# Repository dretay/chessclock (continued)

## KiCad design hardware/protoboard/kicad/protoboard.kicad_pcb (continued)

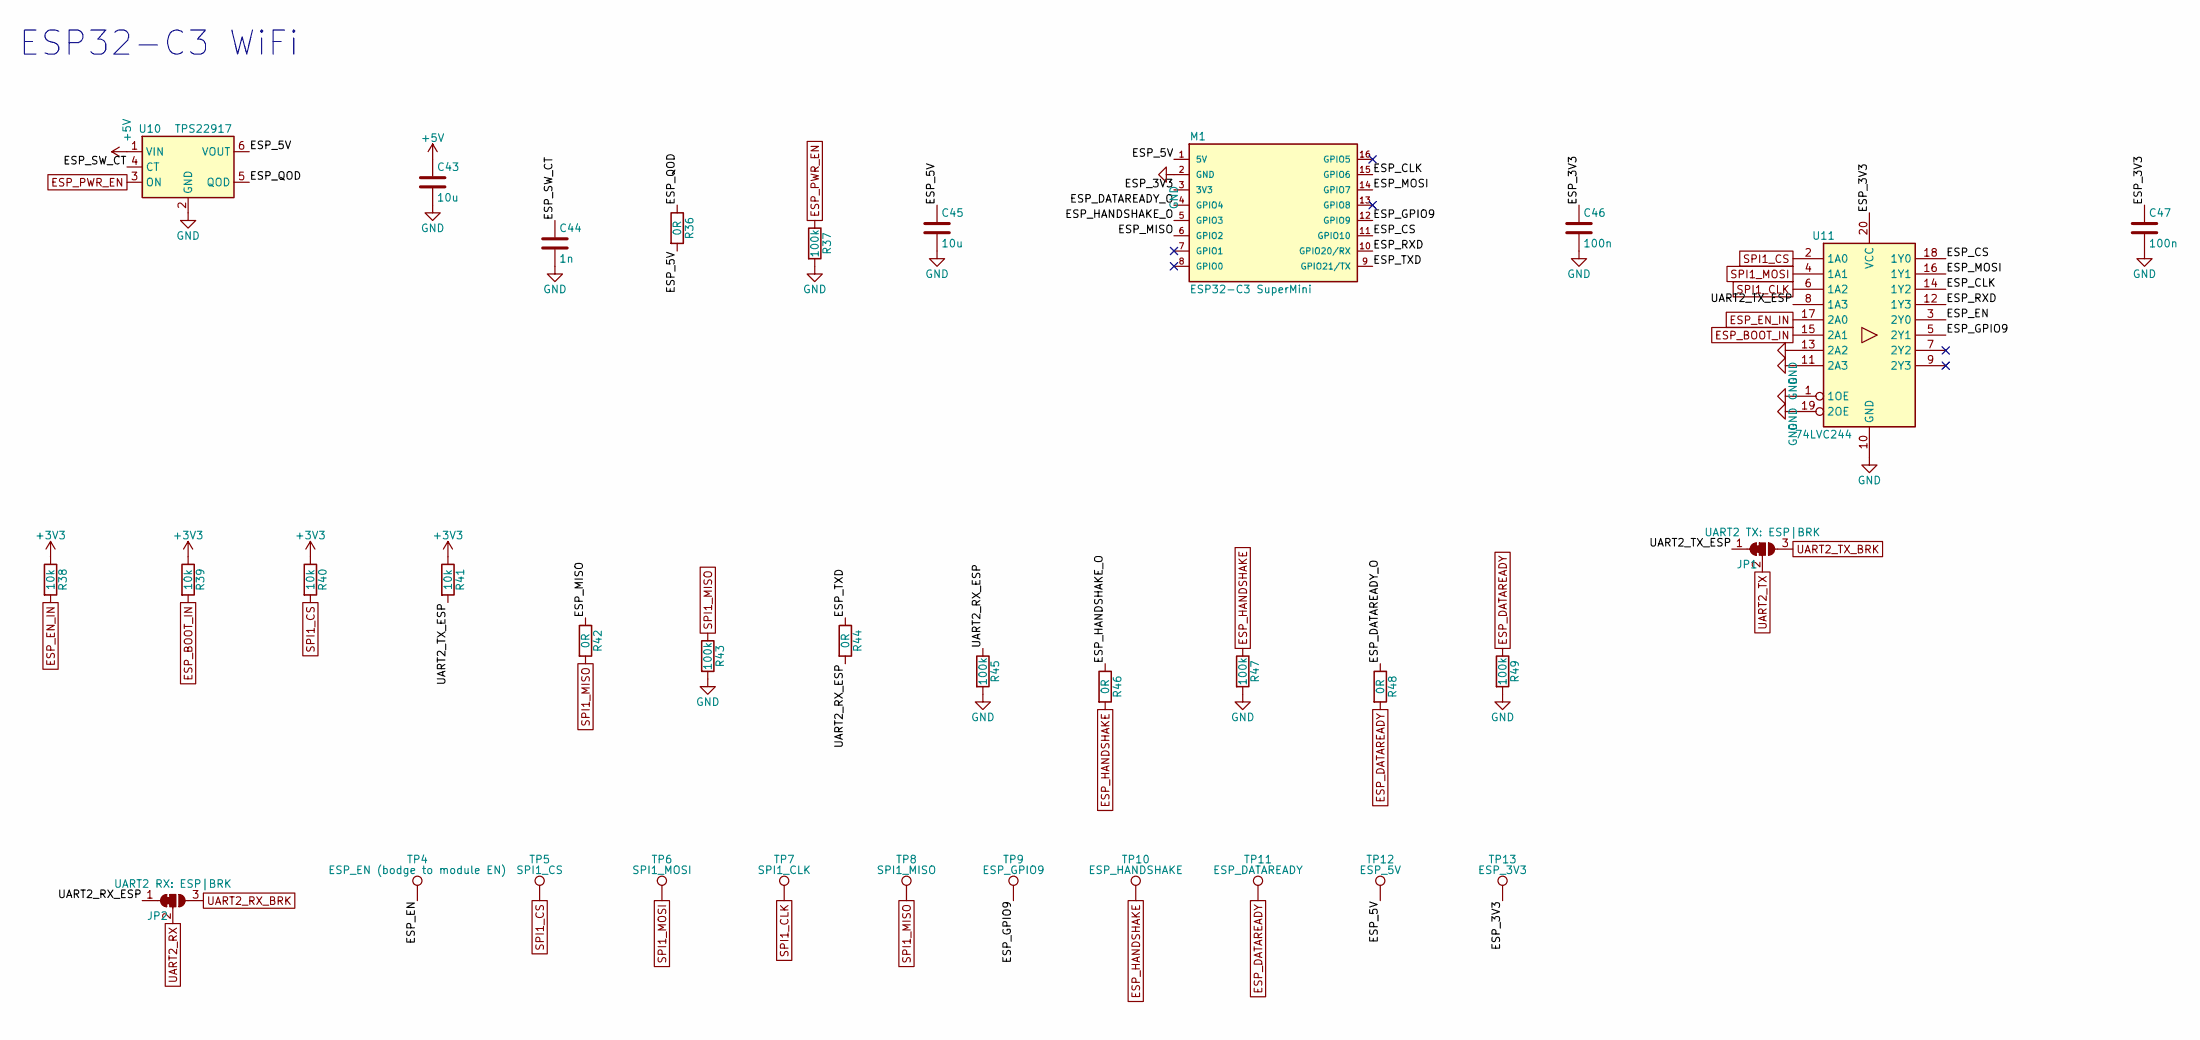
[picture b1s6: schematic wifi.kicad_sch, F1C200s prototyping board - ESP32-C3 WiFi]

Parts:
C43, C45: 10u; C_1206_3216Metric_Pad1.33x1.80mm_HandSolder
C44: 1n; C_0805_2012Metric_Pad1.18x1.45mm_HandSolder
C46, C47: 100n; C_0805_2012Metric_Pad1.18x1.45mm_HandSolder
JP1: UART2 TX: ESP|BRK; SolderJumper-3_P1.3mm_Bridged12_RoundedPad1.0x1.5mm_NumberL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
JP2: UART2 RX: ESP|BRK; SolderJumper-3_P1.3mm_Bridged12_RoundedPad1.0x1.5mm_NumberL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
M1: ESP32-C3 SuperMini; ESP32-C3_SuperMini
R36, R42, R44, R46, R48: 0R; R_0805_2012Metric_Pad1.20x1.40mm_HandSolder
R37, R43, R45, R47, R49: 100k; R_0805_2012Metric_Pad1.20x1.40mm_HandSolder
R38, R39, R40, R41: 10k; R_0805_2012Metric_Pad1.20x1.40mm_HandSolder
TP4: ESP_EN (bodge to module EN); TestPoint_Pad_D1.5mm
TP5: SPI1_CS; TestPoint_Pad_D1.5mm
TP6: SPI1_MOSI; TestPoint_Pad_D1.5mm
TP7: SPI1_CLK; TestPoint_Pad_D1.5mm
TP8: SPI1_MISO; TestPoint_Pad_D1.5mm
TP9: ESP_GPIO9; TestPoint_Pad_D1.5mm
TP10: ESP_HANDSHAKE; TestPoint_Pad_D1.5mm
TP11: ESP_DATAREADY; TestPoint_Pad_D1.5mm
TP12: ESP_5V; TestPoint_Pad_D1.5mm
TP13: ESP_3V3; TestPoint_Pad_D1.5mm
U10: TPS22917; SOT-23-6
U11: 74LVC244; SOIC-20W_7.5x12.8mm_P1.27mm

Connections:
+3V3: R38.1, R39.1, R40.1, R41.1; also elsewhere on the board
+5V: C43.1, U10.1 (VIN); also elsewhere on the board
/ESP32-C3 WiFi/ESP_3V3: C46.1, C47.1, M1.3 (3V3), TP13.1, U11.20 (VCC)
/ESP32-C3 WiFi/ESP_5V: C45.1, M1.1 (5V), R36.2, TP12.1, U10.6 (VOUT)
/ESP32-C3 WiFi/ESP_CLK: M1.15 (GPIO6), U11.14 (1Y2)
/ESP32-C3 WiFi/ESP_CS: M1.11 (GPIO10), U11.18 (1Y0)
/ESP32-C3 WiFi/ESP_DATAREADY_O: M1.4 (GPIO4), R48.1
/ESP32-C3 WiFi/ESP_EN: TP4.1, U11.3 (2Y0)
/ESP32-C3 WiFi/ESP_GPIO9: M1.12 (GPIO9), TP9.1, U11.5 (2Y1)
/ESP32-C3 WiFi/ESP_HANDSHAKE_O: M1.5 (GPIO3), R46.1
/ESP32-C3 WiFi/ESP_MISO: M1.6 (GPIO2), R42.1
/ESP32-C3 WiFi/ESP_MOSI: M1.14 (GPIO7), U11.16 (1Y1)
/ESP32-C3 WiFi/ESP_QOD: R36.1, U10.5 (QOD)
/ESP32-C3 WiFi/ESP_RXD: M1.10 (GPIO20/RX), U11.12 (1Y3)
/ESP32-C3 WiFi/ESP_SW_CT: C44.1, U10.4 (CT)
/ESP32-C3 WiFi/ESP_TXD: M1.9 (GPIO21/TX), R44.1
/ESP32-C3 WiFi/UART2_RX_ESP: JP2.1 (A), R44.2, R45.1
/ESP32-C3 WiFi/UART2_TX_ESP: JP1.1 (A), R41.2, U11.8 (1A3)
ESP_BOOT_IN: R39.2, U11.15 (2A1); also elsewhere on the board
ESP_DATAREADY: R48.2, R49.1, TP11.1; also elsewhere on the board
ESP_EN_IN: R38.2, U11.17 (2A0); also elsewhere on the board
ESP_HANDSHAKE: R46.2, R47.1, TP10.1; also elsewhere on the board
ESP_PWR_EN: R37.1, U10.3 (ON); also elsewhere on the board
GND: C43.2, C44.2, C45.2, C46.2, C47.2, M1.2 (GND), R37.2, R43.2, R45.2, R47.2, R49.2, U10.2 (GND), U11.1 (1OE), U11.10 (GND), U11.11 (2A3), U11.13 (2A2), U11.19 (2OE); also elsewhere on the board
SPI1_CLK: TP7.1, U11.6 (1A2); also elsewhere on the board
SPI1_CS: R40.2, TP5.1, U11.2 (1A0); also elsewhere on the board
SPI1_MISO: R42.2, R43.1, TP8.1; also elsewhere on the board
SPI1_MOSI: TP6.1, U11.4 (1A1); also elsewhere on the board
UART2_RX: JP2.2 (C); also elsewhere on the board
UART2_RX_BRK: JP2.3 (B); also elsewhere on the board
UART2_TX: JP1.2 (C); also elsewhere on the board
UART2_TX_BRK: JP1.3 (B); also elsewhere on the board

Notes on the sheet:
ESP32-C3 WiFi

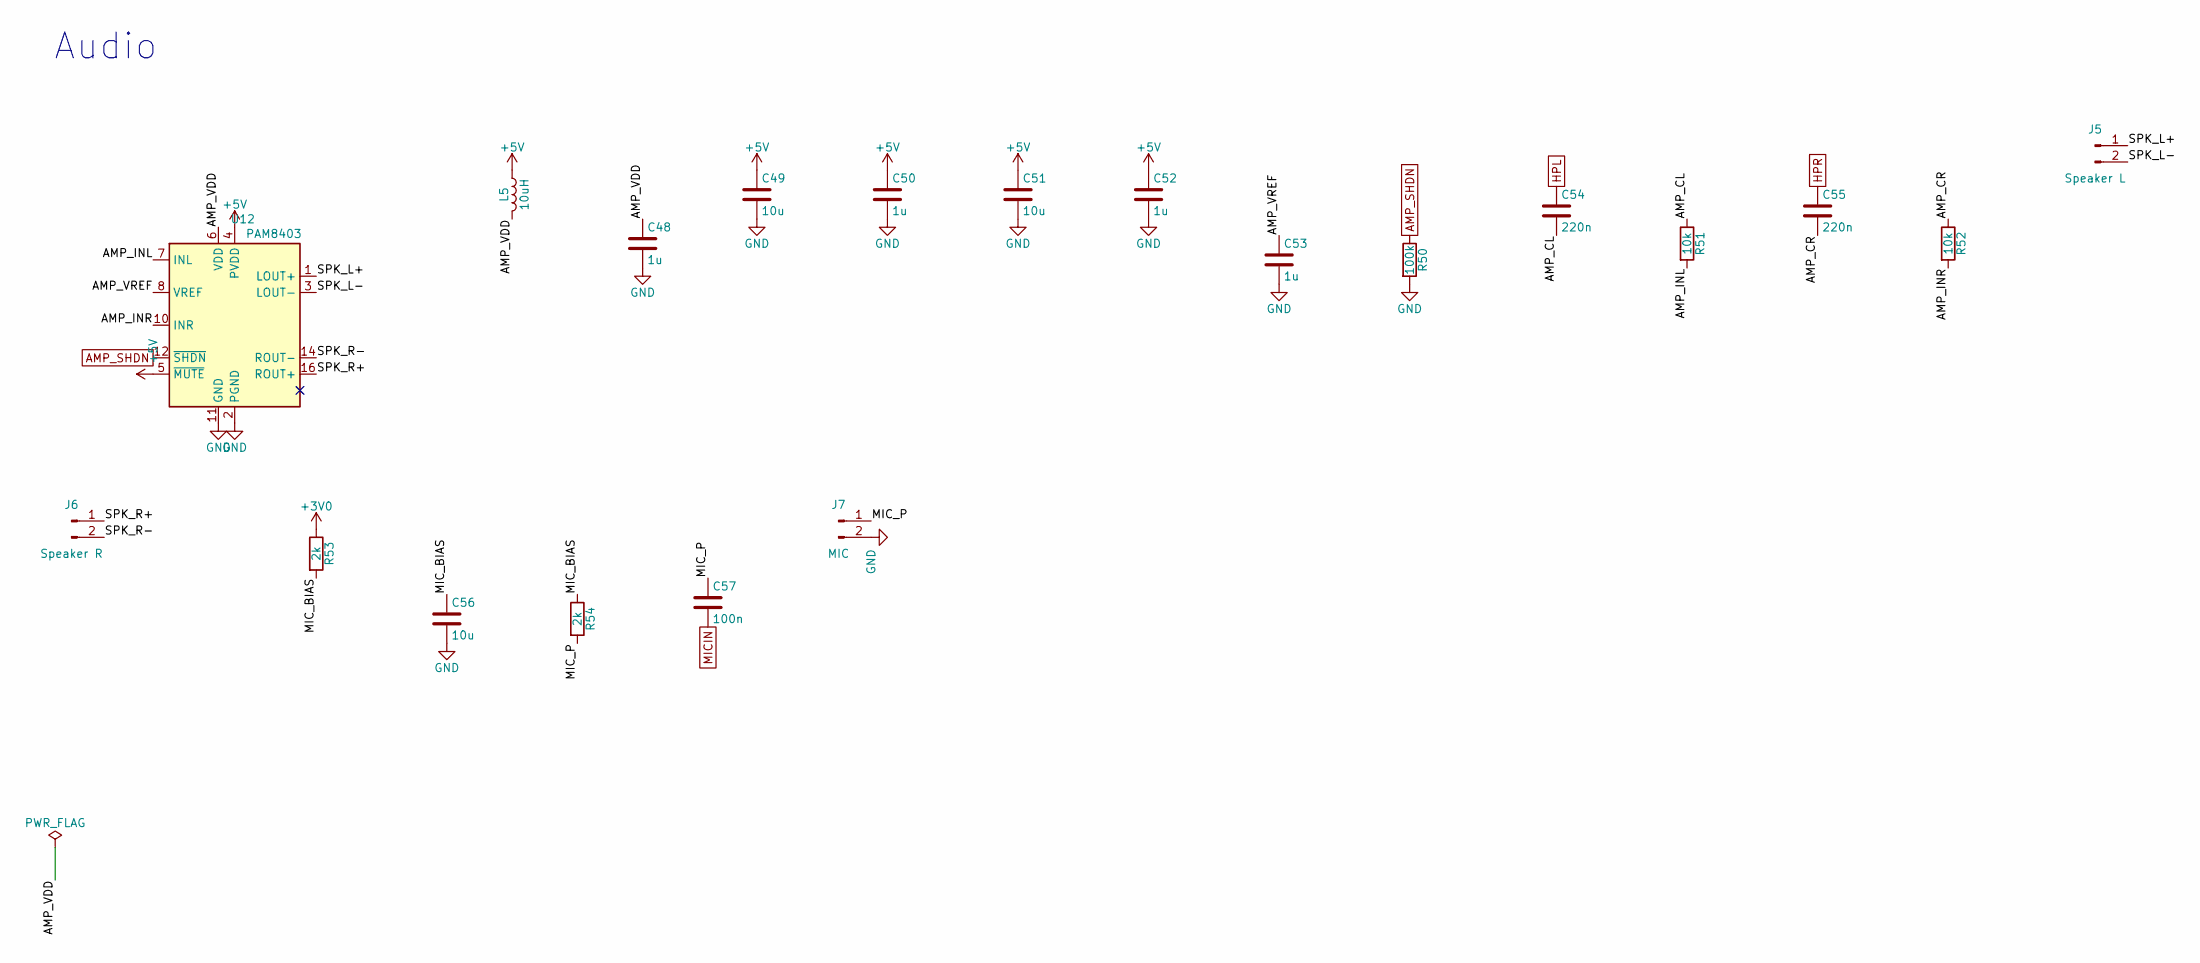
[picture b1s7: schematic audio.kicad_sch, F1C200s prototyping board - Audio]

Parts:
C48, C50, C52, C53: 1u; C_0805_2012Metric_Pad1.18x1.45mm_HandSolder
C49, C51: 10u; C_1206_3216Metric_Pad1.33x1.80mm_HandSolder
C54, C55: 220n; C_0805_2012Metric_Pad1.18x1.45mm_HandSolder
C56: 10u; C_0805_2012Metric_Pad1.18x1.45mm_HandSolder
C57: 100n; C_0805_2012Metric_Pad1.18x1.45mm_HandSolder
J5: Speaker L; JST_PH_B2B-PH-K_1x02_P2.00mm_Vertical
J6: Speaker R; JST_PH_B2B-PH-K_1x02_P2.00mm_Vertical
J7: MIC; PinHeader_1x02_P2.54mm_Vertical
L5: 10uH; L_0805_2012Metric_Pad1.05x1.20mm_HandSolder
R50: 100k; R_0805_2012Metric_Pad1.20x1.40mm_HandSolder
R51, R52: 10k; R_0805_2012Metric_Pad1.20x1.40mm_HandSolder
R53, R54: 2k; R_0805_2012Metric_Pad1.20x1.40mm_HandSolder
U12: PAM8403; SOIC-16_3.9x9.9mm_P1.27mm

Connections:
+3V0: R53.1; also elsewhere on the board
+5V: C49.1, C50.1, C51.1, C52.1, L5.1, U12.4 (PVDD), U12.5 (~MUTE), U12.13 (PVDD); also elsewhere on the board
/Audio/AMP_CL: C54.2, R51.1
/Audio/AMP_CR: C55.2, R52.1
/Audio/AMP_INL: R51.2, U12.7 (INL)
/Audio/AMP_INR: R52.2, U12.10 (INR)
/Audio/AMP_VDD: C48.1, L5.2, U12.6 (VDD)
/Audio/AMP_VREF: C53.1, U12.8 (VREF)
/Audio/MIC_BIAS: C56.1, R53.2, R54.1
/Audio/MIC_P: C57.1, J7.1, R54.2
/Audio/SPK_L+: J5.1, U12.1 (LOUT+)
/Audio/SPK_L-: J5.2, U12.3 (LOUT-)
/Audio/SPK_R+: J6.1, U12.16 (ROUT+)
/Audio/SPK_R-: J6.2, U12.14 (ROUT-)
AMP_SHDN: R50.1, U12.12 (~SHDN); also elsewhere on the board
GND: C48.2, C49.2, C50.2, C51.2, C52.2, C53.2, C56.2, J7.2, R50.2, U12.2 (PGND), U12.11 (GND), U12.15 (PGND); also elsewhere on the board
HPL: C54.1; also elsewhere on the board
HPR: C55.1; also elsewhere on the board
MICIN: C57.2; also elsewhere on the board

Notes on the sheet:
Audio

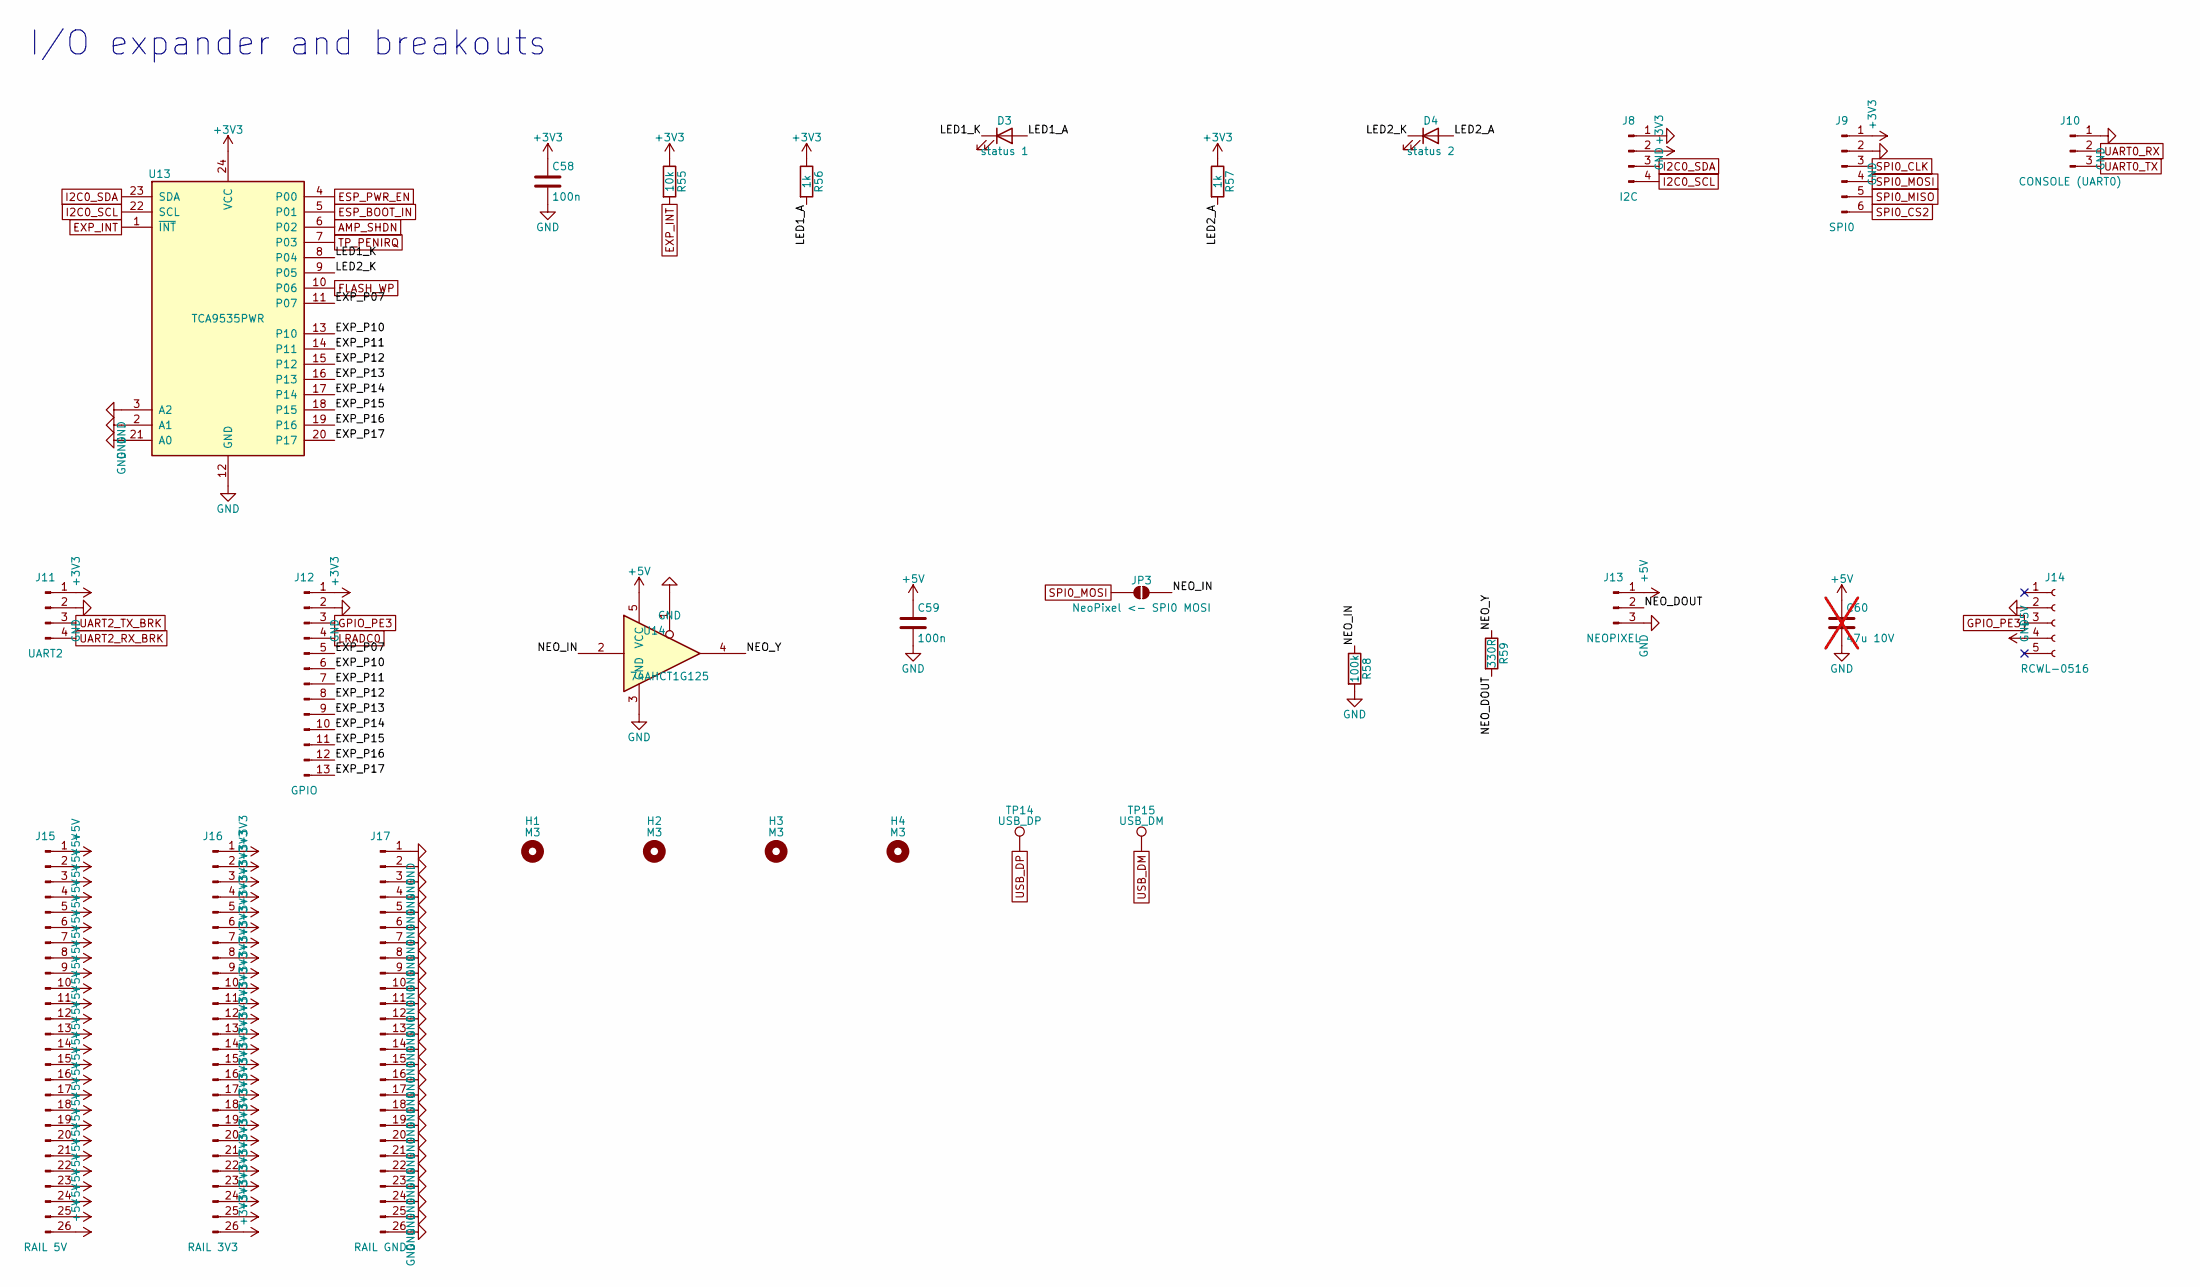
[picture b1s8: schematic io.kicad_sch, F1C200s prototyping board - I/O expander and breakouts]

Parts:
C58, C59: 100n; C_0805_2012Metric_Pad1.18x1.45mm_HandSolder
C60: 47u 10V; C_1210_3225Metric_Pad1.33x2.70mm_HandSolder; not fitted
D3: status 1; LED_0805_2012Metric_Pad1.15x1.40mm_HandSolder
D4: status 2; LED_0805_2012Metric_Pad1.15x1.40mm_HandSolder
H1, H2, H3, H4: M3; MountingHole_3.2mm_M3
J8: I2C; PinHeader_1x04_P2.54mm_Vertical
J9: SPI0; PinHeader_1x06_P2.54mm_Vertical
J10: CONSOLE (UART0); PinHeader_1x03_P2.54mm_Vertical
J11: UART2; PinHeader_1x04_P2.54mm_Vertical
J12: GPIO; PinHeader_1x13_P2.54mm_Vertical
J13: NEOPIXEL; PinHeader_1x03_P2.54mm_Vertical
J14: RCWL-0516; PinSocket_1x05_P2.54mm_Vertical
J15: RAIL 5V; RailStrip_1x26_P2.54mm
J16: RAIL 3V3; RailStrip_1x26_P2.54mm
J17: RAIL GND; RailStrip_1x26_P2.54mm
JP3: NeoPixel <- SPI0 MOSI; SolderJumper-2_P1.3mm_Open_RoundedPad1.0x1.5mm
R55: 10k; R_0805_2012Metric_Pad1.20x1.40mm_HandSolder
R56, R57: 1k; R_0805_2012Metric_Pad1.20x1.40mm_HandSolder
R58: 100k; R_0805_2012Metric_Pad1.20x1.40mm_HandSolder
R59: 330R; R_0805_2012Metric_Pad1.20x1.40mm_HandSolder
TP14: USB_DP; TestPoint_Pad_D1.5mm
TP15: USB_DM; TestPoint_Pad_D1.5mm
U13: TCA9535PWR; TSSOP-24_4.4x7.8mm_P0.65mm
U14: 74AHCT1G125; SOT-23-5

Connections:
+3V3: C58.1, J8.2, J9.1, J11.1, J12.1, J16.1, J16.2, J16.3, J16.4, J16.5, J16.6, J16.7, J16.8, J16.9, J16.10, J16.11, J16.12, J16.13, J16.14, J16.15, J16.16, J16.17, J16.18, J16.19, J16.20, J16.21, J16.22, J16.23, J16.24, J16.25, J16.26, R55.1, R56.1, R57.1, U13.24 (VCC); also elsewhere on the board
+5V: C59.1, C60.1, J13.1, J14.4, J15.1, J15.2, J15.3, J15.4, J15.5, J15.6, J15.7, J15.8, J15.9, J15.10, J15.11, J15.12, J15.13, J15.14, J15.15, J15.16, J15.17, J15.18, J15.19, J15.20, J15.21, J15.22, J15.23, J15.24, J15.25, J15.26, U14.5 (VCC); also elsewhere on the board
/I/O expander and breakouts/EXP_P07: J12.5, U13.11 (P07)
/I/O expander and breakouts/EXP_P10: J12.6, U13.13 (P10)
/I/O expander and breakouts/EXP_P11: J12.7, U13.14 (P11)
/I/O expander and breakouts/EXP_P12: J12.8, U13.15 (P12)
/I/O expander and breakouts/EXP_P13: J12.9, U13.16 (P13)
/I/O expander and breakouts/EXP_P14: J12.10, U13.17 (P14)
/I/O expander and breakouts/EXP_P15: J12.11, U13.18 (P15)
/I/O expander and breakouts/EXP_P16: J12.12, U13.19 (P16)
/I/O expander and breakouts/EXP_P17: J12.13, U13.20 (P17)
/I/O expander and breakouts/LED1_A: D3.2 (A), R56.2
/I/O expander and breakouts/LED1_K: D3.1 (K), U13.8 (P04)
/I/O expander and breakouts/LED2_A: D4.2 (A), R57.2
/I/O expander and breakouts/LED2_K: D4.1 (K), U13.9 (P05)
/I/O expander and breakouts/NEO_DOUT: J13.2, R59.2
/I/O expander and breakouts/NEO_IN: JP3.2 (B), R58.1, U14.2
/I/O expander and breakouts/NEO_Y: R59.1, U14.4
AMP_SHDN: U13.6 (P02); also elsewhere on the board
ESP_BOOT_IN: U13.5 (P01); also elsewhere on the board
ESP_PWR_EN: U13.4 (P00); also elsewhere on the board
EXP_INT: R55.2, U13.1 (~INT); also elsewhere on the board
FLASH_WP: U13.10 (P06); also elsewhere on the board
GND: C58.2, C59.2, C60.2, J8.1, J9.2, J10.1, J11.2, J12.2, J13.3, J14.2, J17.1, J17.2, J17.3, J17.4, J17.5, J17.6, J17.7, J17.8, J17.9, J17.10, J17.11, J17.12, J17.13, J17.14, J17.15, J17.16, J17.17, J17.18, J17.19, J17.20, J17.21, J17.22, J17.23, J17.24, J17.25, J17.26, R58.2, U13.2 (A1), U13.3 (A2), U13.12 (GND), U13.21 (A0), U14.1, U14.3 (GND); also elsewhere on the board
GPIO_PE3: J12.3, J14.3; also elsewhere on the board
I2C0_SCL: J8.4, U13.22 (SCL); also elsewhere on the board
I2C0_SDA: J8.3, U13.23 (SDA); also elsewhere on the board
LRADC0: J12.4; also elsewhere on the board
SPI0_CLK: J9.3; also elsewhere on the board
SPI0_CS2: J9.6; also elsewhere on the board
SPI0_MISO: J9.5; also elsewhere on the board
SPI0_MOSI: J9.4, JP3.1 (A); also elsewhere on the board
TP_PENIRQ: U13.7 (P03); also elsewhere on the board
UART0_RX: J10.2; also elsewhere on the board
UART0_TX: J10.3; also elsewhere on the board
UART2_RX_BRK: J11.4; also elsewhere on the board
UART2_TX_BRK: J11.3; also elsewhere on the board
USB_DM: TP15.1; also elsewhere on the board
USB_DP: TP14.1; also elsewhere on the board

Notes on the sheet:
I/O expander and breakouts

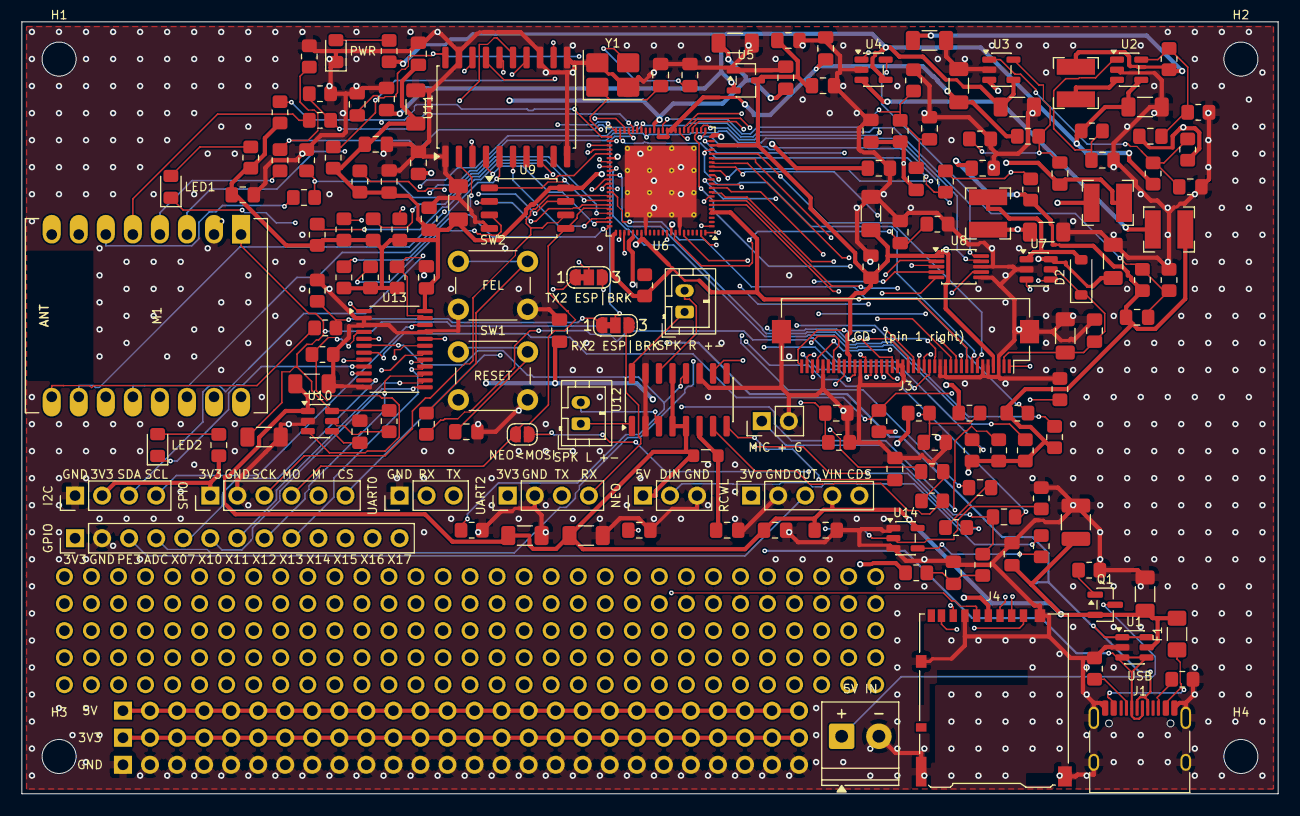
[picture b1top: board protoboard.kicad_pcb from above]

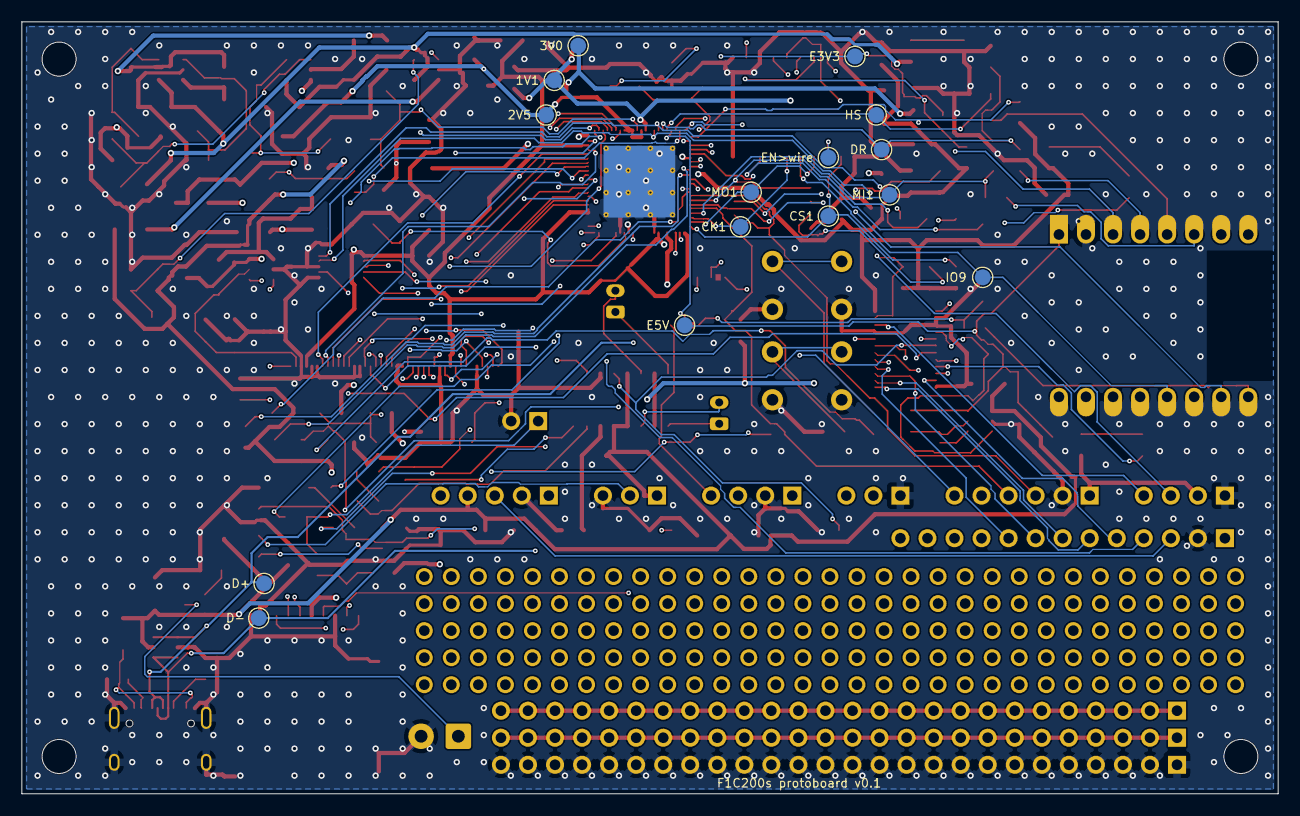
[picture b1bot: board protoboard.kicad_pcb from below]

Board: 4 copper layers, 118.0 x 72.5 mm, 188 parts (15 on the bottom side), 143 nets.

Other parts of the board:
PROTO1: 31 x 5 grid; Protogrid_31x5_P2.54mm

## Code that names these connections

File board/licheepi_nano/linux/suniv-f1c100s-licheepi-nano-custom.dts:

// SPDX-License-Identifier: (GPL-2.0+ OR X11)
//
// Lichee Pi Nano with the 5" 800x480 resistive-touch panel, for mainline
// Linux (6.18). Built on the mainline board file, which already has the SD
// card, SPI flash, USB, serial console and audio codec; this adds what the
// countdown frame needs on top (and SPI WiFi through an ESP32).
//
// The display pipeline (frontend -> backend -> TCON -> panel) is not in
// mainline: the nodes below are carried over from the 5.11 kernel fork this
// board used before (unframework/linux v5.11-nano-4), and need the
// 0001-drm-sun4i-add-F1C100s-display-support.patch kernel patch.

/dts-v1/;
#include "allwinner/suniv-f1c100s-licheepi-nano.dts"
#include <dt-bindings/gpio/gpio.h>

/ {
	model = "Lichee Pi Nano (Custom)";

	de: display-engine {
		compatible = "allwinner,suniv-f1c100s-display-engine";
		allwinner,pipelines = <&fe0>;
		status = "okay";
	};

	panel: panel {
		compatible = "lg,lb070wv8", "simple-panel";
		power-supply = <&reg_vcc3v3>;
		backlight = <&backlight>;

		port {
			panel_input: endpoint {
				remote-endpoint = <&tcon0_out_lcd>;
			};
		};
	};

	// PE6 drives the enable pin of the backlight driver (PT4103, "PWM1" on
	// the schematic), which accepts PWM below 1kHz. Brightness is set
	// through /sys/class/backlight/backlight/brightness.
	backlight: backlight {
		compatible = "pwm-backlight";
		pwms = <&pwm 1 2000000 0>;	// channel 1, 2ms period (500Hz)
		brightness-levels = <0 255>;
		num-interpolated-steps = <255>;
		default-brightness-level = <255>;
	};

	soc {
		fe0: display-frontend@1e00000 {
			compatible = "allwinner,suniv-f1c100s-display-frontend";
			reg = <0x01e00000 0x20000>;
			interrupts = <30>;
			clocks = <&ccu CLK_BUS_DE_FE>, <&ccu CLK_DE_FE>,
				 <&ccu CLK_DRAM_DE_FE>;
			clock-names = "ahb", "mod", "ram";
			resets = <&ccu RST_BUS_DE_FE>;

			ports {
				#address-cells = <1>;
				#size-cells = <0>;

				fe0_out: port@1 {
					#address-cells = <1>;
					#size-cells = <0>;
					reg = <1>;

					fe0_out_be0: endpoint@0 {
						reg = <0>;
						remote-endpoint = <&be0_in_fe0>;
					};
				};
			};
		};

		be0: display-backend@1e60000 {
			compatible = "allwinner,suniv-f1c100s-display-backend";
			reg = <0x01e60000 0x10000>;
			reg-names = "be";
			interrupts = <31>;
			clocks = <&ccu CLK_BUS_DE_BE>, <&ccu CLK_DE_BE>,
				 <&ccu CLK_DRAM_DE_BE>;
			clock-names = "ahb", "mod", "ram";
			resets = <&ccu RST_BUS_DE_BE>;
			reset-names = "be";
			assigned-clocks = <&ccu CLK_DE_BE>;
			assigned-clock-rates = <300000000>;

			ports {
				#address-cells = <1>;
				#size-cells = <0>;

				be0_in: port@0 {
					#address-cells = <1>;
					#size-cells = <0>;
					reg = <0>;

					be0_in_fe0: endpoint@0 {
						reg = <0>;
						remote-endpoint = <&fe0_out_be0>;
					};
				};

				be0_out: port@1 {
					#address-cells = <1>;
					#size-cells = <0>;
					reg = <1>;

					be0_out_tcon0: endpoint@0 {
						reg = <0>;
						remote-endpoint = <&tcon0_in_be0>;
					};
				};
			};
		};

		tcon0: lcd-controller@1c0c000 {
			compatible = "allwinner,suniv-f1c100s-tcon";
			reg = <0x01c0c000 0x1000>;
			interrupts = <29>;
			clocks = <&ccu CLK_BUS_LCD>, <&ccu CLK_TCON>;
			clock-names = "ahb", "tcon-ch0";
			clock-output-names = "tcon-pixel-clock";
			resets = <&ccu RST_BUS_LCD>;
			reset-names = "lcd";
			pinctrl-names = "default";
			pinctrl-0 = <&lcd_rgb666_pins>;

			ports {
				#address-cells = <1>;
				#size-cells = <0>;

				tcon0_in: port@0 {
					#address-cells = <1>;
					#size-cells = <0>;
					reg = <0>;

					tcon0_in_be0: endpoint@0 {
						reg = <0>;
						remote-endpoint = <&be0_out_tcon0>;
					};
				};

				tcon0_out: port@1 {
					#address-cells = <1>;
					#size-cells = <0>;
					reg = <1>;

					tcon0_out_lcd: endpoint@0 {
						reg = <0>;
						remote-endpoint = <&panel_input>;
					};
				};
			};
		};
	};
};

&pio {
	lcd_rgb666_pins: lcd-rgb666-pins {
		pins = "PD0", "PD1", "PD2", "PD3", "PD4",
		       "PD5", "PD6", "PD7", "PD8", "PD9",
		       "PD10", "PD11", "PD12", "PD13", "PD14",
		       "PD15", "PD16", "PD17", "PD18", "PD19",
		       "PD20", "PD21";
		function = "lcd";
	};

	// The resistive touch film (40-pin LCD connector, pins 37-40) goes to
	// the on-board NS2009 touch chip (U4, address 0x48) on TWI0 at PE11/PE12,
	// which the apps read through /dev/i2c-0 (vacation_touch.py). (Mainline only describes
	// TWI0 on PD0/PD12, which collide with the LCD.) The board has no
	// external pull-ups on this bus; without these every transfer times out.
	i2c0_pe_pins: i2c0-pe-pins {
		pins = "PE11", "PE12";
		function = "i2c0";
		bias-pull-up;
	};

	pwm1_pe6_pin: pwm1-pe6-pin {
		pins = "PE6";
		function = "pwm1";
	};

	// SPI1 on the top header's A0-A3 pins, to an ESP32 for WiFi (below)
	spi1_pa_pins: spi1-pa-pins {
		pins = "PA1", "PA2", "PA3";		// MOSI, CLK, MISO
		function = "spi1";
	};

	// CS, with the pin's own pull-up (about 100k) so it stays high (the ESP32 not selected) while
	// nothing drives it, e.g. before Linux sets the pins up. An external 10k to 3.3V is better.
	spi1_cs_pin: spi1-cs-pin {
		pins = "PA0";
		function = "spi1";
		bias-pull-up;
	};
};

// WiFi from an ESP32 running Espressif's ESP-Hosted firmware: Linux sees it
// as wlan0 (driver: esp32_spi.ko, package/esp-hosted-nano). Wiring, Nano header ->
// ESP32 (an MH-ET LIVE MiniKit while testing; the protoboard's ESP32-C3 uses
// the same Nano-side pins):
//   A0 PA0 SPI1 CS (10k pull-up to 3.3V, or just the internal one) -> IO15     A1 PA1 MOSI -> IO13
//   A2 PA2 SPI1 CLK -> IO14                          A3 PA3 MISO <- IO12
//   D6 PE9 <- IO2 handshake    D7 PE10 <- IO4 data ready    PCLK PE2 -> EN
// SPI mode 2. The driver starts at 1 MHz and moves to the speed the firmware
// asks for, capped here: jumper wires don't like much more.
&spi1 {
	pinctrl-names = "default";
	pinctrl-0 = <&spi1_pa_pins>, <&spi1_cs_pin>;
	status = "okay";

	wifi@0 {
		compatible = "espressif,esp32-spi";
		reg = <0>;
		spi-max-frequency = <10000000>;
		spi-cpol;
		reset-gpios = <&pio 4 2 GPIO_ACTIVE_LOW>;		// PE2 -> ESP EN
		handshake-gpios = <&pio 4 9 GPIO_ACTIVE_HIGH>;		// PE9 <- ESP IO2
		data-ready-gpios = <&pio 4 10 GPIO_ACTIVE_HIGH>;	// PE10 <- ESP IO4
	};
};

// The micro-USB port as a USB device only (a serial port for the Mac, see linux_defconfig): no
// host mode, so no need to sense the cable's ID pin, which mainline reads on PE2. That leaves PE2
// free (for the ESP32's reset, above).
&usb_otg {
	dr_mode = "peripheral";
};

&usbphy {
	/delete-property/ usb0_id_det-gpios;
};

&i2c0 {
	pinctrl-names = "default";
	pinctrl-0 = <&i2c0_pe_pins>;
	status = "okay";
};

&pwm {
	pinctrl-names = "default";
	pinctrl-0 = <&pwm1_pe6_pin>;
	status = "okay";
};
